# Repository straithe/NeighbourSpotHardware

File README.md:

# NeighbourSpot
A chonky LED neighbour for GreatFET.

## Description
This GreatFET neighbour is intended to be a very big LED that you can control and lightup from a GreatFET.

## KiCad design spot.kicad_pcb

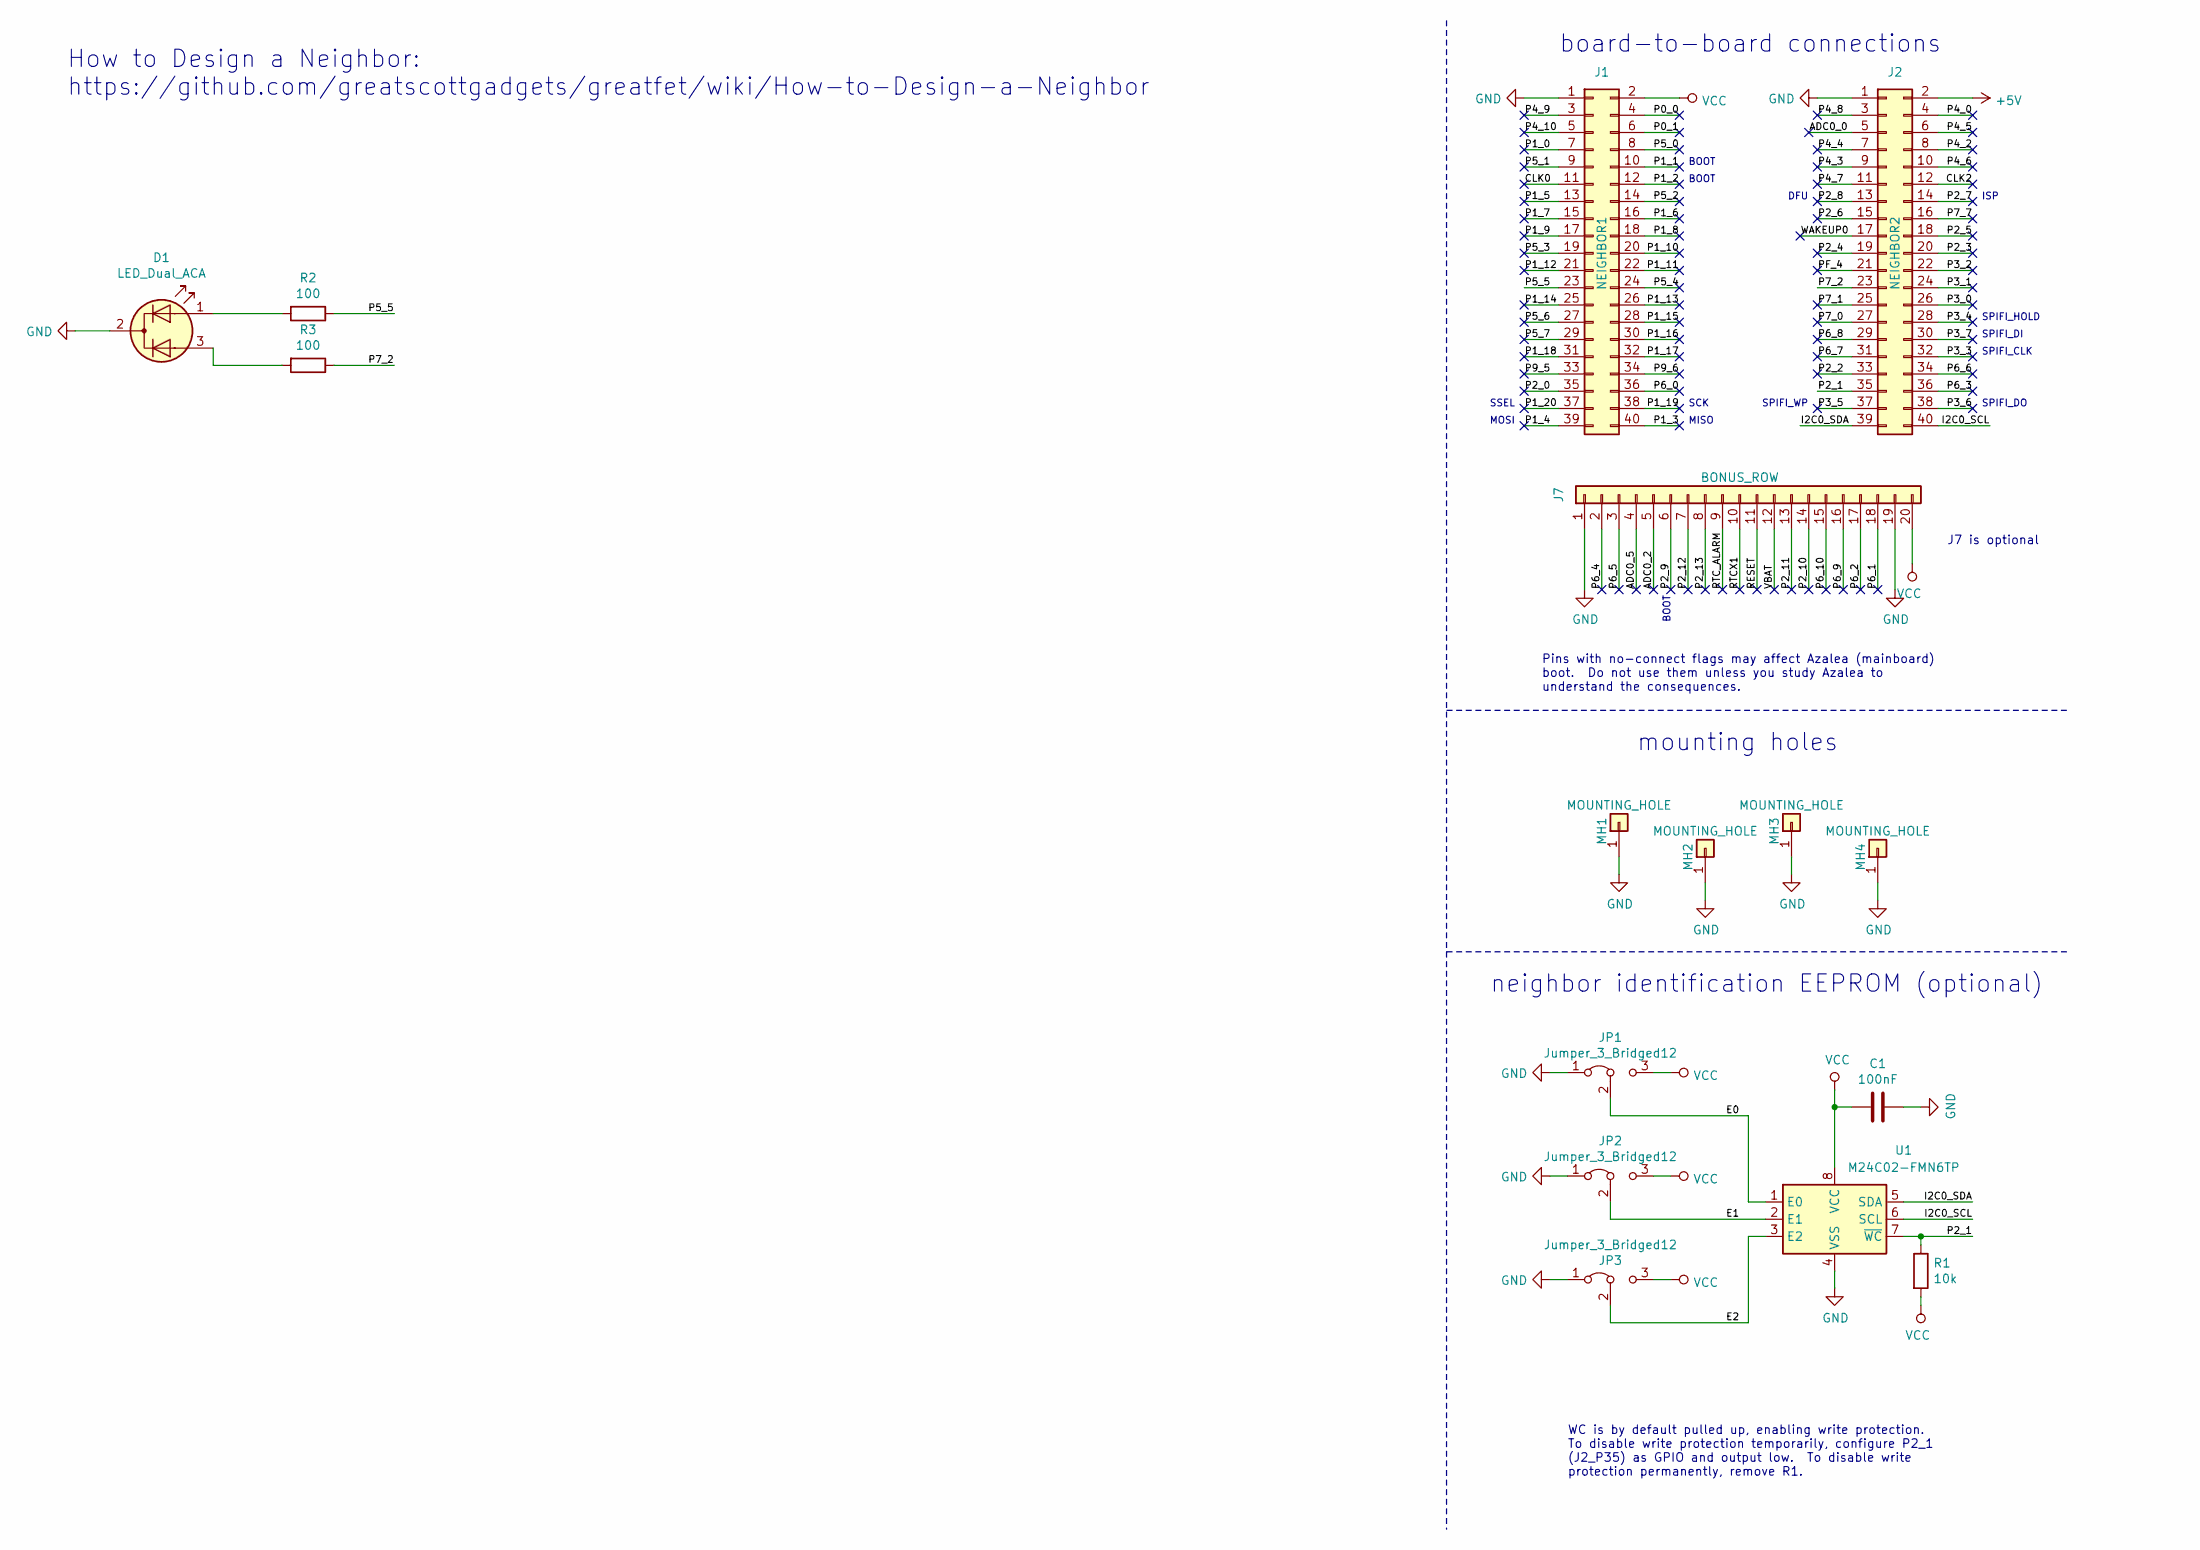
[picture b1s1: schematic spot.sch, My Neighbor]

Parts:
C1: 100nF; C_0603_1608Metric_Pad1.05x0.95mm_HandSolder
D1: LED_Dual_ACA; LED_D10.0mm-3; Part Number 4042
J1: NEIGHBOR1; HEADER-2x20; Part Number SSQ-120-23-G-D
J2: NEIGHBOR2; HEADER-2x20; Part Number SSQ-120-23-G-D
J7: BONUS_ROW; HEADER-1x20; Part Number SSQ-120-23-G-S
JP1, JP2, JP3: Jumper_3_Bridged12; 0603-JUMPER-3-BRIDGED12
MH1, MH2, MH3, MH4: MOUNTING_HOLE; HOLE126MIL-COPPER
R1: 10k; R_0603_1608Metric_Pad1.05x0.95mm_HandSolder
R2, R3: 100; R_Axial_DIN0207_L6.3mm_D2.5mm_P10.16mm_Horizontal
U1: M24C02-FMN6TP; SOIC-8_3.9x4.9mm_P1.27mm

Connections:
+5V: J2.2
/ADC0_0: J2.5
/ADC0_2: J7.5
/ADC0_5: J7.4
/CLK0: J1.11
/CLK2: J2.12
/E0: JP1.2 (C), U1.1 (E0)
/E1: JP2.2 (C), U1.2 (E1)
/E2: JP3.2 (C), U1.3 (E2)
/I2C0_SCL: J2.40, U1.6 (SCL)
/I2C0_SDA: J2.39, U1.5 (SDA)
/P0_0: J1.4
/P0_1: J1.6
/P1_0: J1.7
/P1_1: J1.10
/P1_2: J1.12
/P1_3: J1.40
/P1_4: J1.39
/P1_5: J1.13
/P1_6: J1.16
/P1_7: J1.15
/P1_8: J1.18
/P1_9: J1.17
/P1_10: J1.20
/P1_11: J1.22
/P1_12: J1.21
/P1_13: J1.26
/P1_14: J1.25
/P1_15: J1.28
/P1_16: J1.30
/P1_17: J1.32
/P1_18: J1.31
/P1_19: J1.38
/P1_20: J1.37
/P2_0: J1.35
/P2_1: J2.35, R1.1, U1.7 (~WC)
/P2_2: J2.33
/P2_3: J2.20
/P2_4: J2.19
/P2_5: J2.18
/P2_6: J2.15
/P2_7: J2.14
/P2_8: J2.13
/P2_9: J7.6
/P2_10: J7.14
/P2_11: J7.13
/P2_12: J7.7
/P2_13: J7.8
/P3_0: J2.26
/P3_1: J2.24
/P3_2: J2.22
/P3_3: J2.32
/P3_4: J2.28
/P3_5: J2.37
/P3_6: J2.38
/P3_7: J2.30
/P4_0: J2.4
/P4_2: J2.8
/P4_3: J2.9
/P4_4: J2.7
/P4_5: J2.6
/P4_6: J2.10
/P4_7: J2.11
/P4_8: J2.3
/P4_9: J1.3
/P4_10: J1.5
/P5_0: J1.8
/P5_1: J1.9
/P5_2: J1.14
/P5_3: J1.19
/P5_4: J1.24
/P5_5: J1.23, R2.1
/P5_6: J1.27
/P5_7: J1.29
/P6_0: J1.36
/P6_1: J7.18
/P6_2: J7.17
/P6_3: J2.36
/P6_4: J7.2
/P6_5: J7.3
/P6_6: J2.34
/P6_7: J2.31
/P6_8: J2.29
/P6_9: J7.16
/P6_10: J7.15
/P7_0: J2.27
/P7_1: J2.25
/P7_2: J2.23, R3.1
/P7_7: J2.16
/P9_5: J1.33
/P9_6: J1.34
/PF_4: J2.21
/RESET: J7.11
/RTCX1: J7.10
/RTC_ALARM: J7.9
/VBAT: J7.12
/WAKEUP0: J2.17
GND: C1.1, D1.2 (K), J1.1, J2.1, J7.1, J7.19, JP1.1 (A), JP2.1 (A), JP3.1 (A), MH1.1, MH2.1, MH3.1, MH4.1, U1.4 (VSS)
unnamed: D1.1 (A1), R2.2
unnamed: D1.3 (A2), R3.2
VCC: C1.2, J1.2, J7.20, JP1.3 (B), JP2.3 (B), JP3.3 (B), R1.2, U1.8 (VCC)

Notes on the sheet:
MISO
MOSI
SCK
SSEL
ISP
DFU
BOOT
WC is by default pulled up, enabling write protection. To disable write protection temporarily, configure P2_1 (J2_P35) as GPIO and output low. To disable write protection permanently, remove R1.
SPIFI_CLK
SPIFI_HOLD
SPIFI_WP
SPIFI_DO
SPIFI_DI
Pins with no-connect flags may affect Azalea (mainboard) boot. Do not use them unless you study Azalea to understand the consequences.
board-to-board connections
mounting holes
J7 is optional
How to Design a Neighbor: https://github.com/greatscottgadgets/greatfet/wiki/How-to-Design-a-Neighbor
neighbor identification EEPROM (optional)

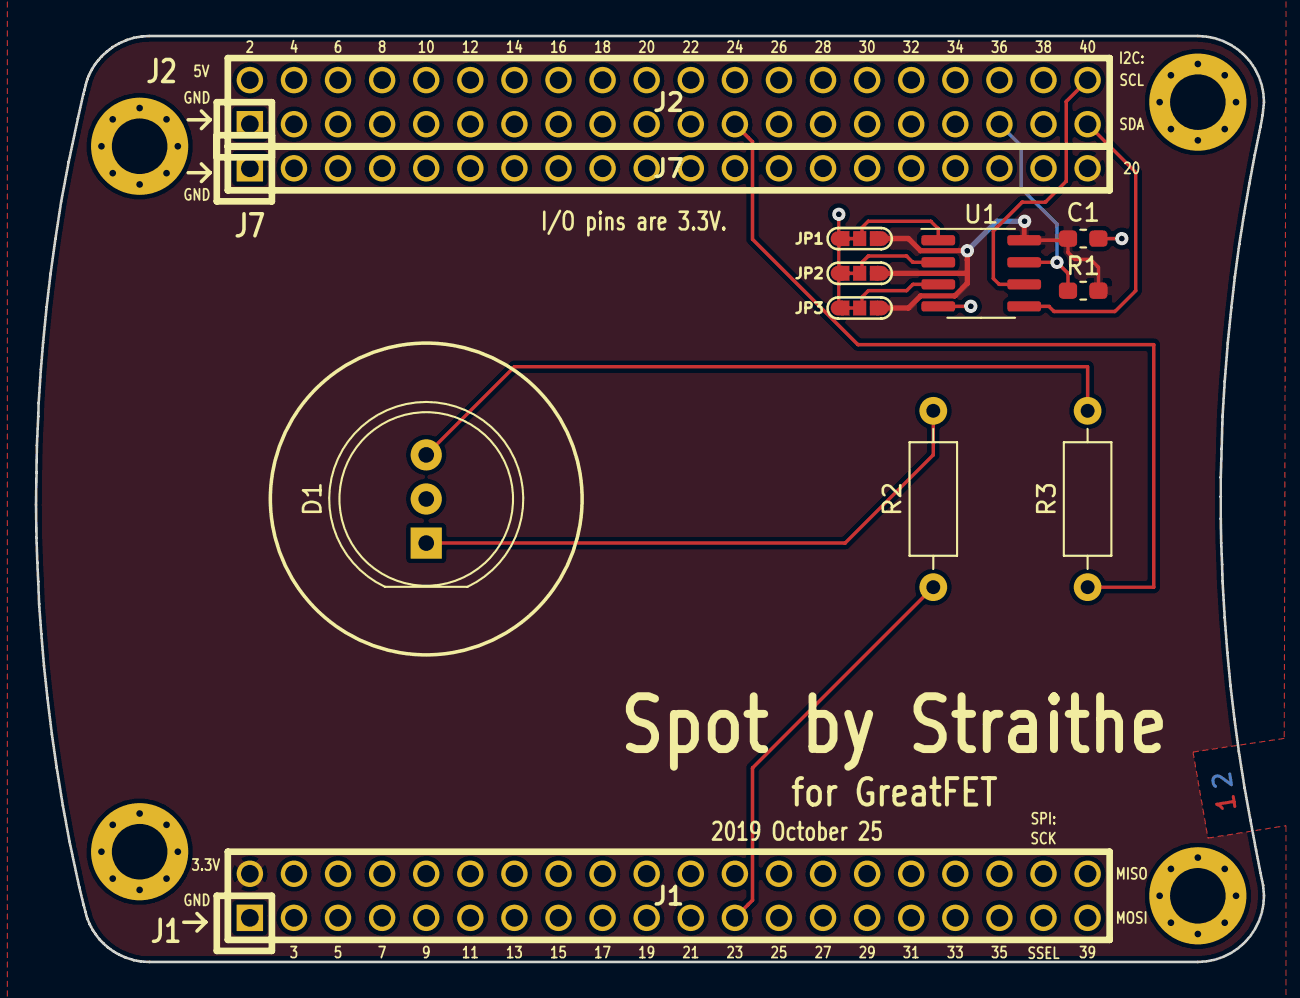
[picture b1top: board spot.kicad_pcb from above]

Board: 2 copper layers, 70.7 x 53.3 mm, 16 parts (0 on the bottom side), 12 nets.

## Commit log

2019-10-26 Added Spot KiCAD files.
